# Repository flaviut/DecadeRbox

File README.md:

# KA-3 Decade Box

This contains the source code for a decade box built with the KM2 thumbwheel
switches. These KM2 switches can be sourced from typical China exporters, like
AliExpress. Typical prices are $3.5-$5 per 10 piece lot.

It has been re-designed from scratch to make use of a fully open-source
toolchain, KiCad & FreeCAD. The break-before-make varient is not supported by
this revision.

## Getting Started

If you're just looking to manufacture some of these boards, check out the
gerbers in `exports/`. <!-- WIP: There are two sets of gerbers: an under
100x100mm panel, and a single board -->

You will also want to buy 9 of each power of ten resistor. The resistors are
all SMD 1206 package, and are designed to dissipate up to a quarter watt each.

## Directory Strucure

This directory contains the CAD files.

`reverse-engineering/` contains the files used to come up with the correct
board outline.

`exports/` contains the output files, in a format where they can be sent to the
manufactuer.

## Credits & License

- [Original Design © Piotr Zapart, 2016][og]. [CC-BY-SA-3.0][]
- [Make-before-break design by Dave, 2016][mbb-dave]

[og]: https://github.com/hexeguitar/DecadeRbox
[CC-BY-SA-3.0]: https://creativecommons.org/licenses/by-sa/3.0/
[mbb-dave]: https://www.eevblog.com/forum/projects/yet-another-resistance-decade-box/msg941946/#msg941946

You may use any part of this project under the [CC-BY-SA-3.0][] license.

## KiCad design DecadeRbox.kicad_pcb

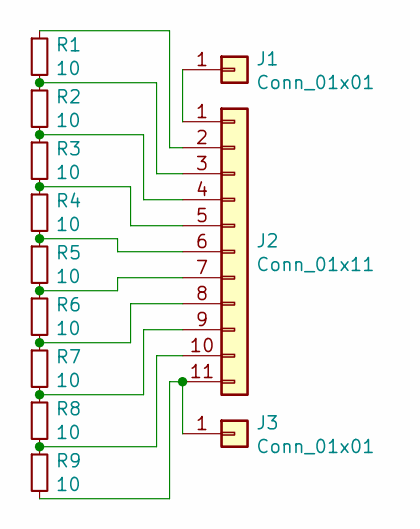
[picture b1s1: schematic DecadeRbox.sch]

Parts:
J1, J3: Conn_01x01; SolderWirePad_1x01_Drill1mm
J2: Conn_01x11; SwitchPad
R1, R2, R3, R4, R5, R6, R7, R8, R9: 10; R_1206_3216Metric

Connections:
unnamed: J1.1, J2.1
unnamed: J2.2, R1.1
unnamed: J2.3, R1.2, R2.1
unnamed: J2.4, R2.2, R3.1
unnamed: J2.5, R3.2, R4.1
unnamed: J2.6, R4.2, R5.1
unnamed: J2.7, R5.2, R6.1
unnamed: J2.8, R6.2, R7.1
unnamed: J2.9, R7.2, R8.1
unnamed: J2.10, R8.2, R9.1
unnamed: J2.11, J3.1, R9.2

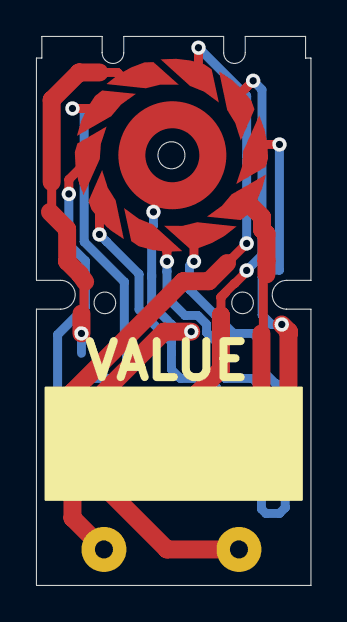
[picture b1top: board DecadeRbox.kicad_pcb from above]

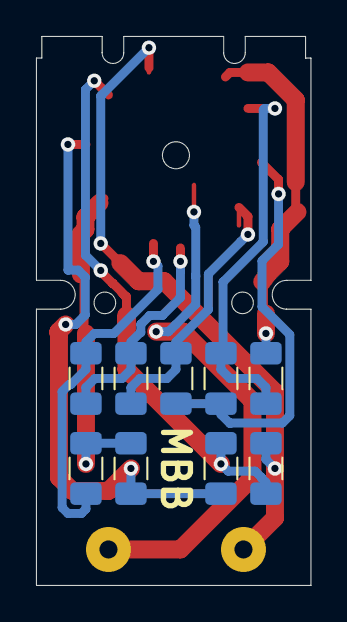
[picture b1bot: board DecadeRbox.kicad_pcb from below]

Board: 2 copper layers, 15.2 x 30.5 mm, 12 parts (9 on the bottom side), 11 nets.

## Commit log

2020-01-04 Begin porting box to kicad/freecad
2020-01-04 Thicken some traces where possible
2020-01-04 Update docs
